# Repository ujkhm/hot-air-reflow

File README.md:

# hot-air-reflow

A closed-loop hot-air reflow oven for double-sided SMT, built from scratch. The controller is an STM32F103C8T6. The mechanical model, control board, and firmware live in this repository.

#### 繁體中文說明在 [README.zh-TW.md](README.zh-TW.md)。

## Layout

```
hot-air-reflow
├── FreeCAD/                      oven model (save the FCStd here)
├── KiCad/hot-air-reflow/         control board
├── BOM/                          bills of materials
├── Code/STM32/hot-air-reflow/    STM32CubeIDE + HAL firmware
└── scripts/                      read coordinates and sync aliases
```

Board-analysis output stays in `KiCad/hot-air-reflow/analysis/`, next to the KiCad project.

## License

[MIT](LICENSE)

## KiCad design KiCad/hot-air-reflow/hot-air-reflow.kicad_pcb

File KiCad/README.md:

# KiCad

控制板用 KiCad 畫，專案在 `hot-air-reflow/`。目標是 JLCPCB 雙層板，長寬都 ≤ 100 mm，控制器 STM32F103C8T6。

分析結果放在該專案的 `analysis/`。

備份、快取和 `*.kicad_prl` 由 `.gitignore` 排除，跟其他專案同一套規則。

[回到主頁](../README.zh-TW.md)

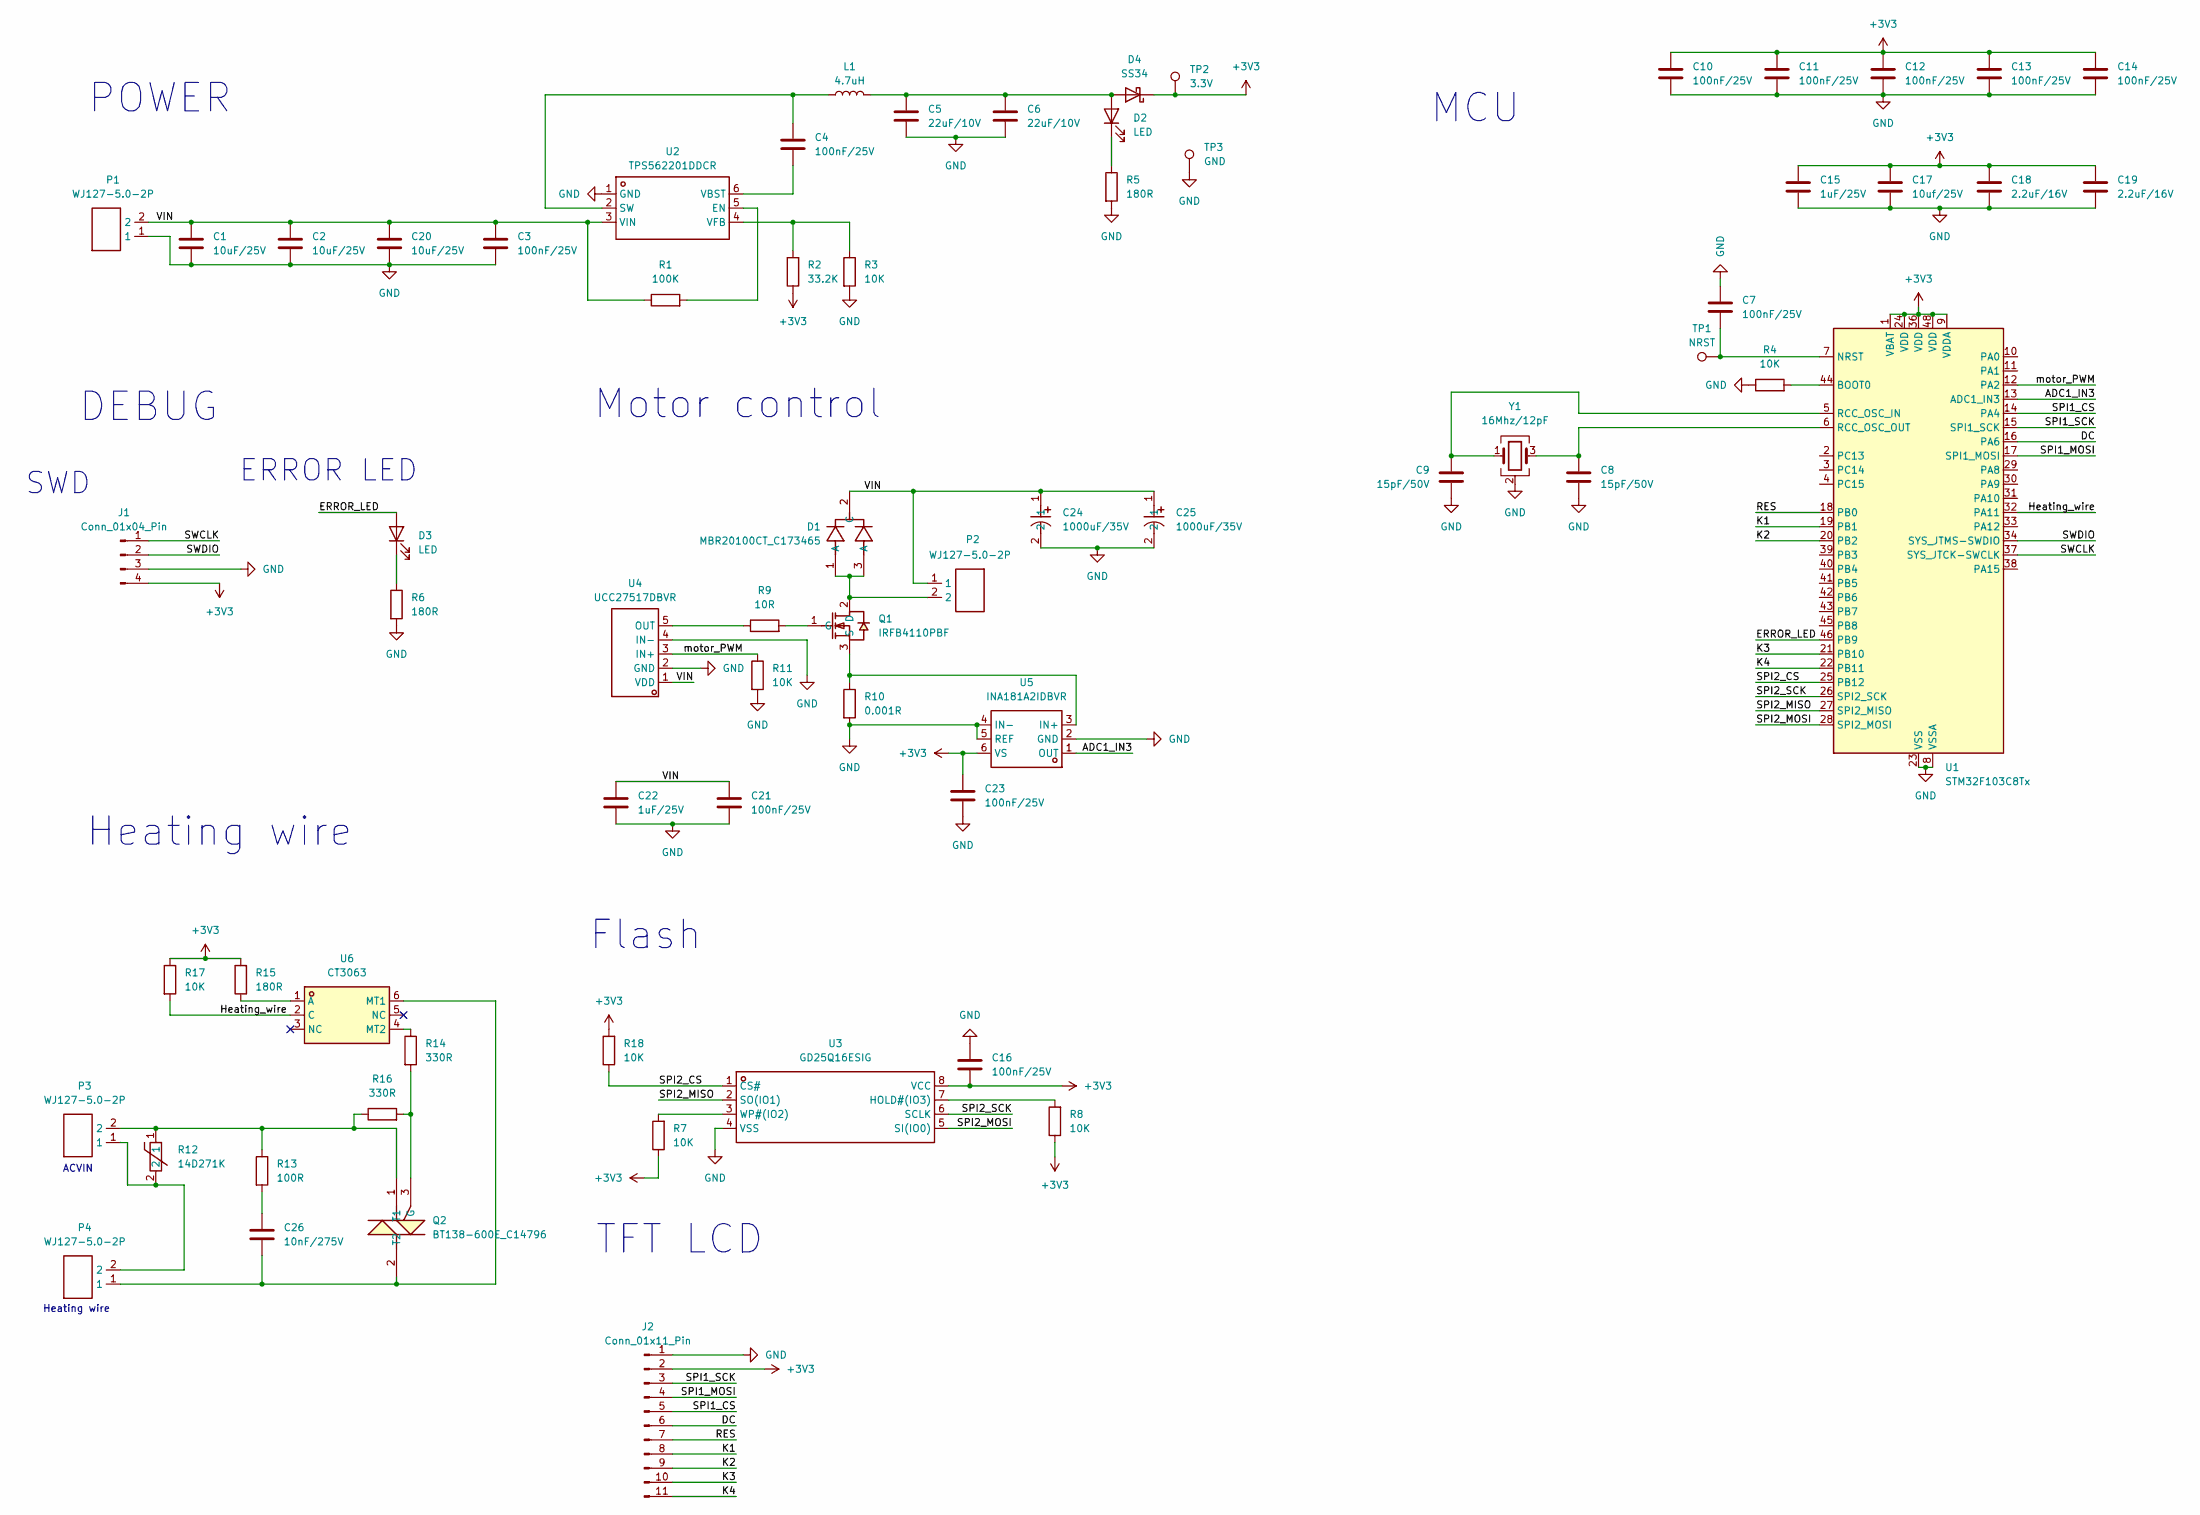
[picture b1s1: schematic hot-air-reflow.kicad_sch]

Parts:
C1, C2, C20: 10uF/25V; C_1206_3216Metric
C3, C4, C7, C10, C11, C12, C13, C14, C16, C21, C23: 100nF/25V; C_0603_1608Metric
C5, C6: 22uF/10V; C_1206_3216Metric
C8, C9: 15pF/50V; C_0603_1608Metric
C15, C22: 1uF/25V; C_0603_1608Metric
C17: 10uf/25V; C_0805_2012Metric
C18, C19: 2.2uF/16V; C_0603_1608Metric
C24, C25: 1000uF/35V; CAP-TH_BD10.0-P5.00-D1.0-FD; LCSC Part C49232884
C26: 10nF/275V; C_Rect_L13.0mm_W5.0mm_P10.00mm_FKS3_FKP3_MKS4
D1: MBR20100CT_C173465; TO-220AB-3_L10.4-W4.6-P2.54-T; LCSC Part C173465
D2, D3: LED; LED_0603_1608Metric
D4: SS34; D_SMA
J1: Conn_01x04_Pin; PinHeader_1x04_P2.54mm_Vertical
J2: Conn_01x11_Pin; PinHeader_1x11_P2.54mm_Vertical
L1: 4.7uH; L_Bourns_SRP7028A_7.3x6.6mm
P1, P2, P3, P4: WJ127-5.0-2P; CONN-TH_2P-P5.00_CPC3703CTR; LCSC Part C3703
Q1: IRFB4110PBF; TO-220-3_L10.0-W4.5-P2.54-L; LCSC Part C2650
Q2: BT138-600E_C14796; TO-220-3_L10.0-W4.5-P2.54-L; LCSC Part C14796
R1: 100K; R_0603_1608Metric
R2: 33.2K; R_0603_1608Metric
R3, R4, R7, R8, R11, R17, R18: 10K; R_0603_1608Metric
R5, R6, R15: 180R; R_0603_1608Metric
R9: 10R; R_0603_1608Metric
R10: 0.001R; R_2512_6332Metric
R12: 14D271K; RES-TH_L16.0-W5.1-P7.50-D0.8-S2.40; LCSC Part C49072888
R13: 100R; R_Axial_DIN0414_L11.9mm_D4.5mm_P15.24mm_Horizontal
R14, R16: 330R; R_0805_2012Metric
TP1: NRST; TestPoint_Pad_D1.5mm
TP2: 3.3V; TestPoint_Pad_D1.5mm
TP3: GND; TestPoint_Pad_D1.5mm
U1: STM32F103C8Tx; LQFP-48_7x7mm_P0.5mm
U2: TPS562201DDCR; SOT-23-6_L2.9-W1.6-P0.95-LS2.8-BR; LCSC Part C90061
U3: GD25Q16ESIG; SOP-8_L5.3-W5.3-P1.27-LS8.0-BL; LCSC Part C2693492
U4: UCC27517DBVR; SOT-23-5_L3.0-W1.7-P0.95-LS2.8-BR; LCSC Part C99395
U5: INA181A2IDBVR; SOT-23-6_L2.9-W1.6-P0.95-LS2.8-BL; LCSC Part C2058784
U6: CT3063; SOP-6_L7.1-W6.5-P2.54-LS10.1-BL; LCSC Part C191853
Y1: 16Mhz/12pF; Crystal_SMD_3225-4Pin_3.2x2.5mm

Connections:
+3V3: C10.1, C11.1, C12.1, C13.1, C14.1, C15.1, C16.2, C17.1, C18.1, C19.1, C23.1, D4.1 (K), J1.4, J2.2, R2.1, R7.1, R8.1, R15.2, R17.1, R18.2, TP2.1, U1.1 (VBAT), U1.9 (VDDA), U1.24 (VDD), U1.36 (VDD), U1.48 (VDD), U3.8 (VCC), U5.6 (VS)
/ADC1_IN3: U1.13 (ADC1_IN3), U5.1 (OUT)
/DC: J2.6, U1.16 (PA6)
/ERROR_LED: D3.2 (A), U1.46 (PB9)
/Heating_wire: R17.2, U1.32 (PA11), U6.2 (C)
/K1: J2.8, U1.19 (PB1)
/K2: J2.9, U1.20 (PB2)
/K3: J2.10, U1.21 (PB10)
/K4: J2.11, U1.22 (PB11)
/RES: J2.7, U1.18 (PB0)
/SPI1_CS: J2.5, U1.14 (PA4)
/SPI1_MOSI: J2.4, U1.17 (SPI1_MOSI)
/SPI1_SCK: J2.3, U1.15 (SPI1_SCK)
/SPI2_CS: R18.1, U1.25 (PB12), U3.1 (CS#)
/SPI2_MISO: U1.27 (SPI2_MISO), U3.2 (SO(IO1))
/SPI2_MOSI: U1.28 (SPI2_MOSI), U3.5 (SI(IO0))
/SPI2_SCK: U1.26 (SPI2_SCK), U3.6 (SCLK)
/SWCLK: J1.1, U1.37 (SYS_JTCK-SWCLK)
/SWDIO: J1.2, U1.34 (SYS_JTMS-SWDIO)
/VIN: C1.1, C2.1, C3.1, C20.1, C21.1, C22.1, C24.1, C25.1, D1.2 (C), P1.2, P2.1, R1.1, U2.3 (VIN), U4.1 (VDD)
/motor_PWM: R11.1, U1.12 (PA2), U4.3 (IN+)
GND: C1.2, C2.2, C3.2, C5.2, C6.2, C7.1, C8.2, C9.2, C10.2, C11.2, C12.2, C13.2, C14.2, C15.2, C16.1, C17.2, C18.2, C19.2, C20.2, C21.2, C22.2, C23.2, C24.2, C25.2, J1.3, J2.1, P1.1, R3.2, R4.1, R5.2, R6.2, R10.2, R11.2, TP3.1, U1.8 (VSSA), U1.23 (VSS), U1.35 (VSS), U1.47 (VSS), U2.1 (GND), U3.4 (VSS), U4.2 (GND), U4.4 (IN-), U5.2 (GND), U5.4 (IN-), U5.5 (REF), Y1.2 (G), Y1.4 (G)
unnamed: C26.1, R13.2
unnamed: C5.1, C6.1, D2.2 (A), D4.2 (A), L1.2
unnamed: D2.1 (K), R5.1
unnamed: D3.1 (K), R6.1
unnamed: P3.1, P4.2, R12.2
unnamed: D1.1 (A), D1.3 (A), P2.2, Q1.2 (D)
unnamed: Q1.1 (G), R9.2
unnamed: Q1.3 (S), R10.1, U5.3 (IN+)
unnamed: Q2.3 (G), R14.2, R16.2
unnamed: P3.2, Q2.1 (T1), R12.1, R13.1, R16.1
unnamed: C26.2, P4.1, Q2.2 (T2), U6.6 (MT1)
unnamed: R4.2, U1.44 (BOOT0)
unnamed: C7.2, TP1.1, U1.7 (NRST)
unnamed: C9.1, U1.5 (RCC_OSC_IN), Y1.1
unnamed: C8.1, U1.6 (RCC_OSC_OUT), Y1.3
unnamed: R1.2, U2.5 (EN)
unnamed: C4.1, L1.1, U2.2 (SW)
unnamed: C4.2, U2.6 (VBST)
unnamed: R2.2, R3.1, U2.4 (VFB)
unnamed: R8.2, U3.7 (HOLD#(IO3))
unnamed: R7.2, U3.3 (WP#(IO2))
unnamed: R9.1, U4.5 (OUT)
unnamed: R15.1, U6.1 (A)
unnamed: R14.1, U6.4 (MT2)

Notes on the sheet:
ACVIN
TFT LCD
Motor control
Flash
Heating wire
MCU
POWER
SWD
DEBUG
ERROR LED

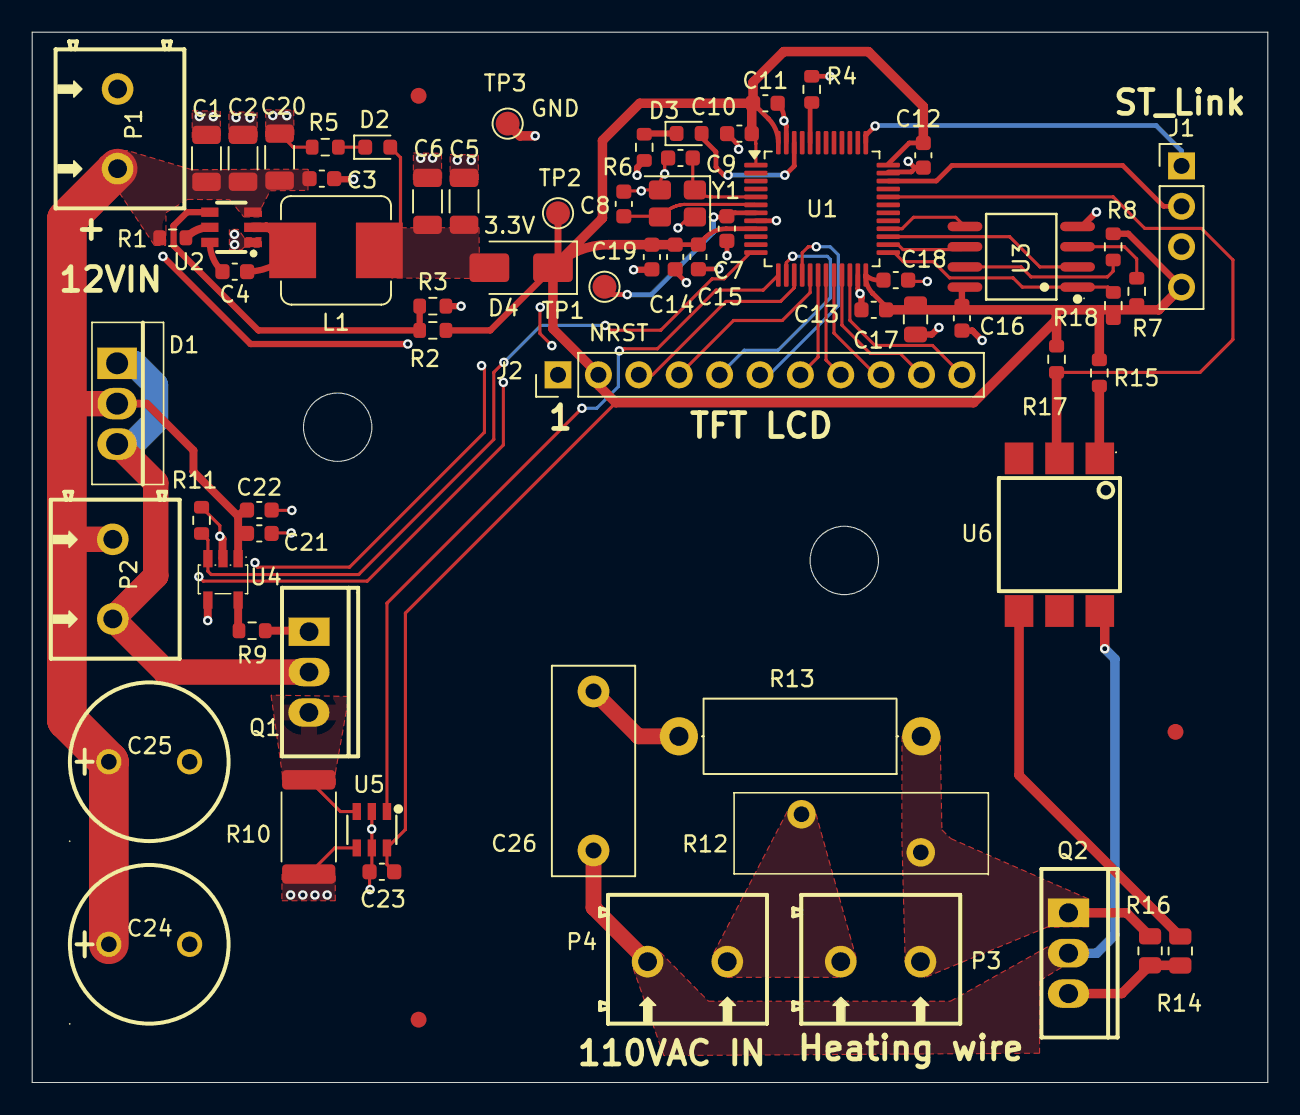
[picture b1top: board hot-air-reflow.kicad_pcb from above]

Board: 2 copper layers, 77.7 x 66.1 mm, 67 parts (0 on the bottom side), 46 nets.

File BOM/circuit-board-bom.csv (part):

"Source:","E:\hot-air-reflow\KiCad\hot-air-reflow\hot-air-reflow.kicad_sch"
"Date:","2026-11-28T10:00:24+0800"
"Tool:","Eeschema 9.0.7"
"Generator:","D:\KiCad\9.0\bin\scripting\plugins\bom_csv_grouped_by_value.py"
"Component Count:","67"

"Collated Components:"

"Item","Qty","Reference(s)","Value","LibPart","Footprint","Datasheet","DNP","Datasheet","Description","Footprint","KLC_S3.3","KLC_S4.1","LCSC Part","Manufacturer","Sim.Pins"
"1","3","C1, C2, C20","10uF/25V","Device:C","Capacitor_SMD:C_1206_3216Metric","~","","~","Unpolarized capacitor","Capacitor_SMD:C_1206_3216Metric","","","","",""
"2","11","C3, C4, C7, C10, C11, C12, C13, C14, C16, C21, C23","100nF/25V","Device:C","Capacitor_SMD:C_0603_1608Metric","~","","~","Unpolarized capacitor","Capacitor_SMD:C_0603_1608Metric","","","","",""
"3","2","C5, C6","22uF/10V","Device:C","Capacitor_SMD:C_1206_3216Metric","~","","~","Unpolarized capacitor","Capacitor_SMD:C_1206_3216Metric","","","","",""
"4","2","C8, C9","15pF/50V","Device:C","Capacitor_SMD:C_0603_1608Metric","~","","~","Unpolarized capacitor","Capacitor_SMD:C_0603_1608Metric","","","","",""
"5","2","C15, C22","1uF/25V","Device:C","Capacitor_SMD:C_0603_1608Metric","~","","~","Unpolarized capacitor","Capacitor_SMD:C_0603_1608Metric","","","","",""
"6","1","C17","10uf/25V","Device:C","Capacitor_SMD:C_0805_2012Metric","~","","~","Unpolarized capacitor","Capacitor_SMD:C_0805_2012Metric","","","","",""
"7","2","C18, C19","2.2uF/16V","Device:C","Capacitor_SMD:C_0603_1608Metric","~","","~","Unpolarized capacitor","Capacitor_SMD:C_0603_1608Metric","","","","",""
"8","2","C24, C25","1000uF/35V","PH35V1000M10X17:PH35V1000M10X17","PH35V1000M10X17:CAP-TH_BD10.0-P5.00-D1.0-FD","","","","PH35V1000M10X17","PH35V1000M10X17:CAP-TH_BD10.0-P5.00-D1.0-FD","","","C49232884","JIERR(捷而瑞)",""
"9","1","C26","10nF/275V","Device:C","Capacitor_THT:C_Rect_L13.0mm_W5.0mm_P10.00mm_FKS3_FKP3_MKS4","~","","~","Unpolarized capacitor","Capacitor_THT:C_Rect_L13.0mm_W5.0mm_P10.00mm_FKS3_FKP3_MKS4","","","","",""
"10","1","D1","MBR20100CT_C173465","MBR20100CT:MBR20100CT_C173465","MBR20100CT:TO-220AB-3_L10.4-W4.6-P2.54-T","https://lcsc.com/product-detail/Schottky-Barrier-Diodes-SBD_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","","https://lcsc.com/product-detail/Schottky-Barrier-Diodes-SBD_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","MBR20100CT","MBR20100CT:TO-220AB-3_L10.4-W4.6-P2.54-T","","","C173465","MDD(辰达半导体)",""
"11","2","D2, D3","LED","Device:LED","LED_SMD:LED_0603_1608Metric","~","","~","Light emitting diode","LED_SMD:LED_0603_1608Metric","","","","","1=K 2=A"
"12","1","D4","SS34","Diode:SS34","Diode_SMD:D_SMA","https://www.vishay.com/docs/88751/ss32.pdf","","https://www.vishay.com/docs/88751/ss32.pdf","40V 3A Schottky Diode, SMA","Diode_SMD:D_SMA","","","","",""
"13","1","J1","Conn_01x04_Pin","Connector:Conn_01x04_Pin","Connector_PinHeader_2.54mm:PinHeader_1x04_P2.54mm_Vertical","~","","~","Generic connector, single row, 01x04, script generated","Connector_PinHeader_2.54mm:PinHeader_1x04_P2.54mm_Vertical","","","","",""
"14","1","J2","Conn_01x11_Pin","Connector:Conn_01x11_Pin","Connector_PinHeader_2.54mm:PinHeader_1x11_P2.54mm_Vertical","~","","~","Generic connector, single row, 01x11, script generated","Connector_PinHeader_2.54mm:PinHeader_1x11_P2.54mm_Vertical","","","","",""
"15","1","L1","4.7uH","Device:L","Inductor_SMD:L_Bourns_SRP7028A_7.3x6.6mm","~","","~","Inductor","Inductor_SMD:L_Bourns_SRP7028A_7.3x6.6mm","","","","",""
"16","4","P1, P2, P3, P4","WJ127-5.0-2P","Terminal-block:WJ127-5.0-2P","Terminal-block:CONN-TH_2P-P5.00_CPC3703CTR","https://lcsc.com/product-detail/Terminal-Blocks_WJ127-5-0-2P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","","https://lcsc.com/product-detail/Terminal-Blocks_WJ127-5-0-2P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","WJ127-5.0-2P","Terminal-block:CONN-TH_2P-P5.00_CPC3703CTR","","","C3703","KANGNEX(康奈克斯电气)",""
"17","1","Q1","IRFB4110PBF","IRFB4110PBF:IRFB4110PBF","IRFB4110PBF:TO-220-3_L10.0-W4.5-P2.54-L","https://lcsc.com/product-detail/MOSFET_IR_IRFB4110PBF_IRFB41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","","https://lcsc.com/product-detail/MOSFET_IR_IRFB4110PBF_IRFB41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","IRFB4110PBF","IRFB4110PBF:TO-220-3_L10.0-W4.5-P2.54-L","","","C2650","Infineon(英飞凌)",""
"18","1","Q2","BT138-600E_C14796","BT138-600E:BT138-600E_C14796","BT138-600E:TO-220-3_L10.0-W4.5-P2.54-L","https://lcsc.com/product-detail/NXP-MCU_NXP_BT138-600E_BT138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","","https://lcsc.com/product-detail/NXP-MCU_NXP_BT138-600E_BT138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","BT138-600E,127","BT138-600E:TO-220-3_L10.0-W4.5-P2.54-L","","","C14796","WeEn(瑞能)",""
"19","1","R1","100K","Device:R","Resistor_SMD:R_0603_1608Metric","~","","~","Resistor","Resistor_SMD:R_0603_1608Metric","","","","",""
"20","1","R2","33.2K","Device:R","Resistor_SMD:R_0603_1608Metric","~","","~","Resistor","Resistor_SMD:R_0603_1608Metric","","","","",""
"21","7","R3, R4, R7, R8, R11, R17, R18","10K","Device:R","Resistor_SMD:R_0603_1608Metric","~","","~","Resistor","Resistor_SMD:R_0603_1608Metric","","","","",""
"22","3","R5, R6, R15","180R","Device:R","Resistor_SMD:R_0603_1608Metric","~","","~","Resistor","Resistor_SMD:R_0603_1608Metric","","","","",""
"23","1","R9","10R","Device:R","Resistor_SMD:R_0603_1608Metric","~","","~","Resistor","Resistor_SMD:R_0603_1608Metric","","","","",""
"24","1","R10","0.001R","Device:R","Resistor_SMD:R_2512_6332Metric","~","","~","Resistor","Resistor_SMD:R_2512_6332Metric","","","","",""
"25","1","R12","14D271K","14D271K:14D271K_C49072888","14D271K:RES-TH_L16.0-W5.1-P7.50-D0.8-S2.40","","","","14D271K","14D271K:RES-TH_L16.0-W5.1-P7.50-D0.8-S2.40","","","C49072888","R+O(宏嘉诚)",""
"26","1","R13","100R","Device:R","Resistor_THT:R_Axial_DIN0414_L11.9mm_D4.5mm_P15.24mm_Horizontal","~","","~","Resistor","Resistor_THT:R_Axial_DIN0414_L11.9mm_D4.5mm_P15.24mm_Horizontal","","","","",""
"27","2","R14, R16","330R","Device:R","Resistor_SMD:R_0805_2012Metric","~","","~","Resistor","Resistor_SMD:R_0805_2012Metric","","","","",""
"28","1","TP1","NRST","Connector:TestPoint","TestPoint:TestPoint_Pad_D1.5mm","~","","~","test point","TestPoint:TestPoint_Pad_D1.5mm","","","","",""
"29","1","TP2","3.3V","Connector:TestPoint","TestPoint:TestPoint_Pad_D1.5mm","~","","~","test point","TestPoint:TestPoint_Pad_D1.5mm","","","","",""
"30","1","TP3","GND","Connector:TestPoint","TestPoint:TestPoint_Pad_D1.5mm","~","","~","test point","TestPoint:TestPoint_Pad_D1.5mm","","","","",""
"31","1","U1","STM32F103C8Tx","MCU_ST_STM32F1:STM32F103C8Tx","Package_QFP:LQFP-48_7x7mm_P0.5mm","https://www.st.com/resource/en/datasheet/stm32f103c8.pdf","","https://www.st.com/resource/en/datasheet/stm32f103c8.pdf","STMicroelectronics Arm Cortex-M3 MCU, 64KB flash, 20KB RAM, 72 MHz, 2.0-3.6V, 37 GPIO, LQFP48","Package_QFP:LQFP-48_7x7mm_P0.5mm","","","","",""
"32","1","U2","TPS562201DDCR","TPS562201DDCR:TPS562201DDCR","TPS562201DDCR:SOT-23-6_L2.9-W1.6-P0.95-LS2.8-BR","https://lcsc.com/product-detail/DC-DC-Converters_TI_TPS56220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","","https://lcsc.com/product-detail/DC-DC-Converters_TI_TPS56220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","TPS562201DDCR","TPS562201DDCR:SOT-23-6_L2.9-W1.6-P0.95-LS2.8-BR","","","C90061","TI(德州仪器)",""
"33","1","U3","GD25Q16ESIG","GD25Q16ESIG:GD25Q16ESIG","GD25Q16ESIG:SOP-8_L5.3-W5.3-P1.27-LS8.0-BL","","","","GD25Q16ESIG","GD25Q16ESIG:SOP-8_L5.3-W5.3-P1.27-LS8.0-BL","","","C2693492","GigaDevice(兆易创新)",""
"34","1","U4","UCC27517DBVR","UCC27517DBVR:UCC27517DBVR","UCC27517DBVR:SOT-23-5_L3.0-W1.7-P0.95-LS2.8-BR","https://lcsc.com/product-detail/MOS-Drivers_TI_UCC27517DBVR_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","","https://lcsc.com/product-detail/MOS-Drivers_TI_UCC27517DBVR_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","UCC27517DBVR","UCC27517DBVR:SOT-23-5_L3.0-W1.7-P0.95-LS2.8-BR","","","C99395","TI(德州仪器)",""
"35","1","U5","INA181A2IDBVR","INA181A2IDBVR:INA181A2IDBVR","INA181A2IDBVR:SOT-23-6_L2.9-W1.6-P0.95-LS2.8-BL","","","","INA181A2IDBVR","INA181A2IDBVR:SOT-23-6_L2.9-W1.6-P0.95-LS2.8-BL","","","C2058784","TI(德州仪器)",""
"36","1","U6","CT3063","CT3063:CT3063_C191853","CT3063:SOP-6_L7.1-W6.5-P2.54-LS10.1-BL","https://lcsc.com/product-detail/Others_CT-Micro-Internationa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","","https://lcsc.com/product-detail/Others_CT-Micro-Internationa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","CT3063(S)(T1)","CT3063:SOP-6_L7.1-W6.5-P2.54-LS10.1-BL","","","C191853","CT MICRO",""
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
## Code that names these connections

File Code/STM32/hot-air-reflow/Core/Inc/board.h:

#ifndef BOARD_H
#define BOARD_H

#include <stdbool.h>
#include <stdint.h>

/*
 * Pins match the control-board netlist (U1 on hot-air-reflow.kicad_pcb).
 *
 * PA2  motor_PWM   fan low-side switch, via U4 into Q1. High turns the fan on.
 * PA3  ADC1_IN3    U5 INA181A2 output. Gain 50, shunt R10 = 1 mOhm.
 * PA4  SPI1_CS     display chip select, idle high
 * PA5  SPI1_SCK    display clock
 * PA6  DC          display data/command. High = data.
 * PA7  SPI1_MOSI   display data
 * PB0  RES         display reset, active low
 * PB1  K1          keys, idle high, pressed = low
 * PB2  K2
 * PB10 K3
 * PB11 K4
 * PB12 SPI2_CS     GD25Q16 chip select, idle high
 * PB13 SPI2_SCK
 * PB14 SPI2_MISO
 * PB15 SPI2_MOSI
 * PC13 ERROR_LED   D3 anode. High lights the LED.
 *
 * U6 (heater optocoupler) and Q2 (triac) are not connected to the MCU.
 */

void board_init(void);

void board_error_led(bool on);

/* permille: 0 is off, 1000 is fully on. Larger values are clamped. */
void board_fan_set(uint16_t permille);
uint16_t board_fan_get(void);

/* Fan current in milliamps, from the shunt amplifier. */
int32_t board_fan_current_ma(void);

/* Bit 0 is K1 .. bit 3 is K4. A set bit means that key is pressed. */
uint8_t board_keys(void);

void board_disp_cs(bool selected);
void board_disp_dc(bool data);
int board_disp_write(const uint8_t *data, uint16_t length);

void board_flash_cs(bool selected);
int board_flash_transfer(const uint8_t *tx, uint8_t *rx, uint16_t length);

#endif
